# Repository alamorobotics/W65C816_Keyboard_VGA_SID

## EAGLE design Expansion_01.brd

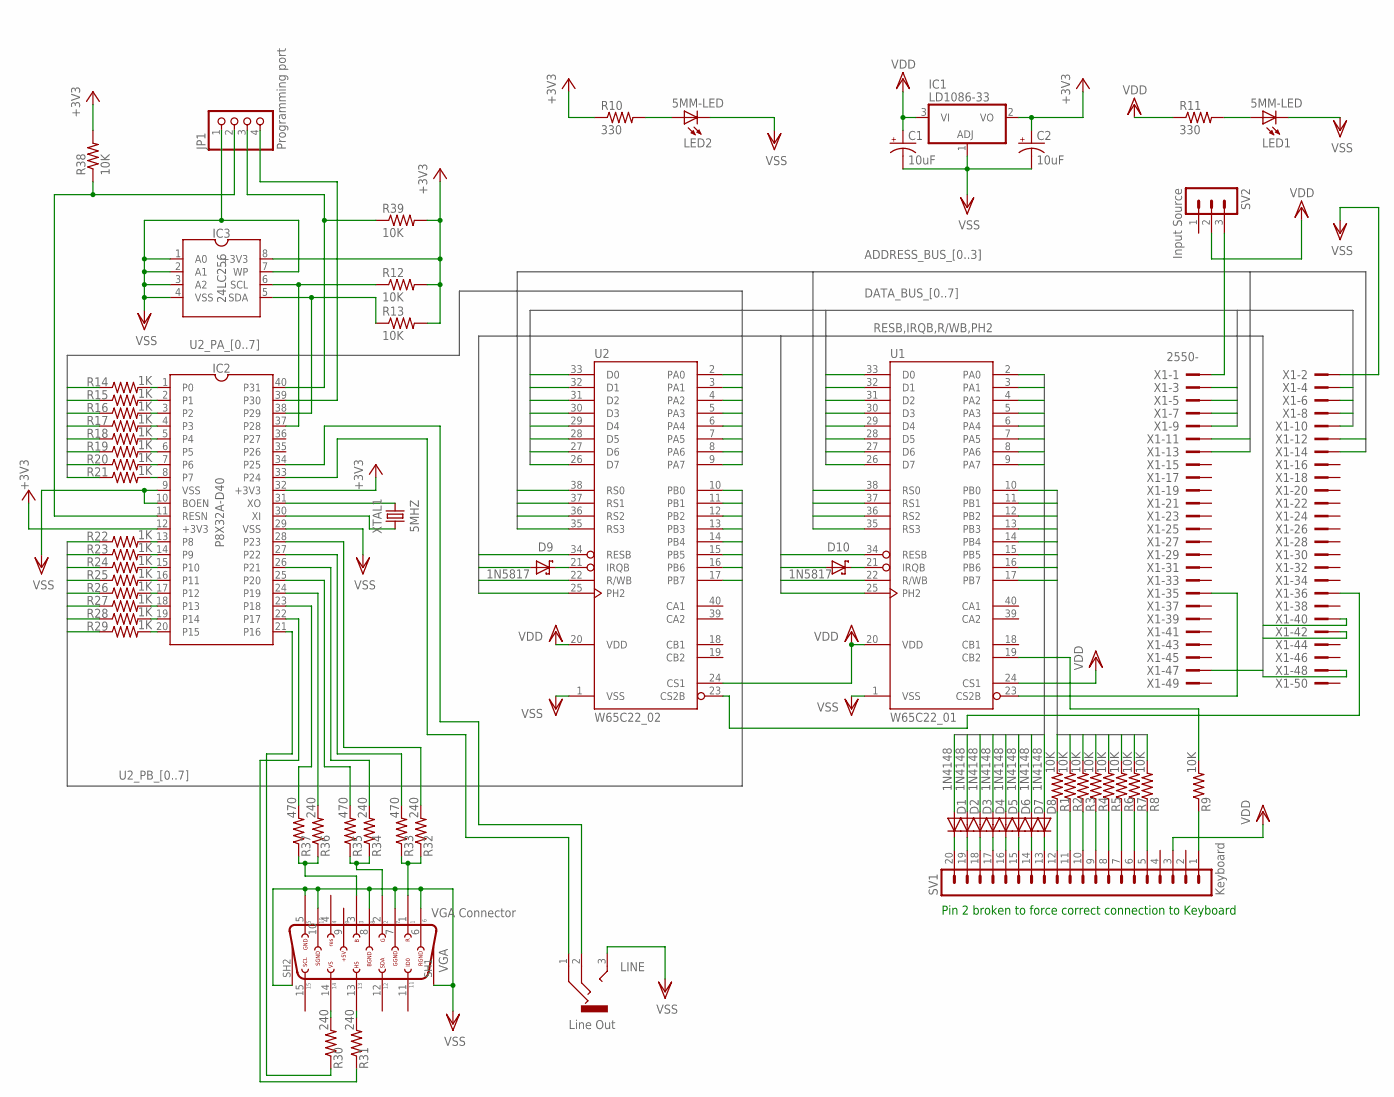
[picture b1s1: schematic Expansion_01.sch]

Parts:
C1, C2: 10uF; E2-5
D1, D2, D3, D4, D5, D6, D7, D8: 1N4148; DO35-7
D9, D10: 1N5817; DO41-7.6
IC1: LD1086-33; TO220H
IC2: P8X32A-D40DIP-40; P8X32A-D40
IC3: 24LC256DIP-8; 24LC256
JP1: Programming port; 1X04/90
LED1, LED2: 5MM-LED
LINE: Line Out; 1503_04
R1, R2, R3, R4, R5, R6, R7, R8, R9, R12, R13, R38, R39: 10K; 0207/10
R10, R11: 330; 0207/10
R14, R15, R16, R17, R18, R19, R20, R21, R22, R23, R24, R25, R26, R27, R28, R29: 1K; 0207/10
R30, R31, R32, R34, R36: 240; 0207/10
R33, R35, R37: 470; 0207/10
SV1: Keyboard; MA20-1
SV2: Input Source; MA03-1
U1: W65C22_01; DIP-40
U2: W65C22_02; DIP-40
VGA: VGA Connector; HD15F
X1: 2550-; PAK100/2500-50
XTAL1: 5MHZ; 5MHZ-CRYSTAL

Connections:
+3V3: C2.+, IC1.2 (VO), IC2.12 (+3V3), IC2.32 (+3V3), IC3.8 (+3V3), R10.1, R12.2, R13.2, R38.2, R39.2
ADDRESS_BUS_0: U1.38 (RS0), U2.38 (RS0), X1.11
ADDRESS_BUS_1: U1.37 (RS1), U2.37 (RS1), X1.12
ADDRESS_BUS_2: U1.36 (RS2), U2.36 (RS2), X1.13
ADDRESS_BUS_3: U1.35 (RS3), U2.35 (RS3), X1.14
DATA_BUS_0: U1.33 (D0), U2.33 (D0), X1.3, X1.4
DATA_BUS_1: U1.32 (D1), U2.32 (D1)
DATA_BUS_2: U1.31 (D2), U2.31 (D2), X1.5
DATA_BUS_3: U1.30 (D3), U2.30 (D3), X1.6
DATA_BUS_4: U1.29 (D4), U2.29 (D4), X1.7
DATA_BUS_5: U1.28 (D5), U2.28 (D5), X1.8
DATA_BUS_6: U1.27 (D6), U2.27 (D6), X1.9
DATA_BUS_7: U1.26 (D7), U2.26 (D7), X1.10
IRQB: D9.A, D10.A, X1.40
unnamed: SV2.3, X1.1
unnamed: D1.C, SV1.20
unnamed: D2.C, SV1.19
unnamed: D3.C, SV1.18
unnamed: D4.C, SV1.17
unnamed: D5.C, SV1.16
unnamed: D6.C, SV1.15
unnamed: D7.C, SV1.14
unnamed: D8.C, SV1.13
unnamed: R1.1, SV1.12
unnamed: R2.1, SV1.11
unnamed: R3.1, SV1.10
unnamed: R4.1, SV1.9
unnamed: R5.1, SV1.8
unnamed: R6.1, SV1.7
unnamed: R7.1, SV1.6
unnamed: R8.1, SV1.5
unnamed: R9.1, SV1.1
unnamed: R9.2, U1.19 (CB2)
unnamed: D10.C, U1.21 (IRQB)
unnamed: D9.C, U2.21 (IRQB)
unnamed: U1.23 (CS2B), X1.35
unnamed: U2.23 (CS2B), X1.36
unnamed: LED1.A, R11.2
unnamed: LED2.A, R10.2
unnamed: IC2.40 (P31), JP1.3, R39.1
unnamed: IC2.39 (P30), JP1.4
unnamed: IC2.31 (XO), XTAL1.2
unnamed: IC2.30 (XI), XTAL1.1
unnamed: IC2.11 (RESN), JP1.2, R38.1
unnamed: IC2.38 (P29), IC3.5 (SDA), R13.1
unnamed: IC2.37 (P28), IC3.6 (SCL), R12.1
unnamed: IC2.1 (P0), R14.2
unnamed: IC2.2 (P1), R15.2
unnamed: IC2.3 (P2), R16.2
unnamed: IC2.4 (P3), R17.2
unnamed: IC2.5 (P4), R18.2
unnamed: IC2.6 (P5), R19.2
unnamed: IC2.7 (P6), R20.2
unnamed: IC2.8 (P7), R21.2
unnamed: IC2.13 (P8), R22.2
unnamed: IC2.14 (P9), R23.2
unnamed: IC2.15 (P10), R24.2
unnamed: IC2.16 (P11), R25.2
unnamed: IC2.17 (P12), R26.2
unnamed: IC2.18 (P13), R27.2
unnamed: IC2.19 (P14), R28.2
unnamed: IC2.20 (P15), R29.2
unnamed: R32.1, R33.1, VGA.1
unnamed: R34.1, R35.1, VGA.2
unnamed: R36.1, R37.1, VGA.3
unnamed: IC2.23 (P18), R37.2
unnamed: IC2.22 (P17), R31.1
unnamed: R30.2, VGA.14
unnamed: R31.2, VGA.13
unnamed: IC2.21 (P16), R30.1
unnamed: IC2.24 (P19), R36.2
unnamed: IC2.25 (P20), R35.2
unnamed: IC2.26 (P21), R34.2
unnamed: IC2.27 (P22), R33.2
unnamed: IC2.28 (P23), R32.2
unnamed: IC2.33 (P24), LINE.1
unnamed: IC2.34 (P25), LINE.2 (3)
PH2: U1.25 (PH2), U2.25 (PH2), X1.48
R/WB: U1.22 (R/WB), U2.22 (R/WB), X1.47
RESB: U1.34 (RESB), U2.34 (RESB), X1.42
U1_PA_0: D1.A, U1.2 (PA0)
U1_PA_1: D2.A, U1.3 (PA1)
U1_PA_2: D3.A, U1.4 (PA2)
U1_PA_3: D4.A, U1.5 (PA3)
U1_PA_4: D5.A, U1.6 (PA4)
U1_PA_5: D6.A, U1.7 (PA5)
U1_PA_6: D7.A, U1.8 (PA6)
U1_PA_7: D8.A, U1.9 (PA7)
U1_PB_0: R1.2, U1.10 (PB0)
U1_PB_1: R2.2, U1.11 (PB1)
U1_PB_2: R3.2, U1.12 (PB2)
U1_PB_3: R4.2, U1.13 (PB3)
U1_PB_4: R5.2, U1.14 (PB4)
U1_PB_5: R6.2, U1.15 (PB5)
U1_PB_6: R7.2, U1.16 (PB6)
U1_PB_7: R8.2, U1.17 (PB7)
U2_PA_0: R14.1, U2.2 (PA0)
U2_PA_1: R15.1, U2.3 (PA1)
U2_PA_2: R16.1, U2.4 (PA2)
U2_PA_3: R17.1, U2.5 (PA3)
U2_PA_4: R18.1, U2.6 (PA4)
U2_PA_5: R19.1, U2.7 (PA5)
U2_PA_6: R20.1, U2.8 (PA6)
U2_PA_7: R21.1, U2.9 (PA7)
U2_PB_0: R22.1, U2.10 (PB0)
U2_PB_1: R23.1, U2.11 (PB1)
U2_PB_2: R24.1, U2.12 (PB2)
U2_PB_3: R25.1, U2.13 (PB3)
U2_PB_4: R26.1, U2.14 (PB4)
U2_PB_5: R27.1, U2.15 (PB5)
U2_PB_6: R28.1, U2.16 (PB6)
U2_PB_7: R29.1, U2.17 (PB7)
VDD: C1.+, IC1.3 (VI), R11.1, SV1.3, SV2.2, U1.20 (VDD), U1.24 (CS1), U2.20 (VDD), U2.24 (CS1)
VSS: C1.-, C2.-, IC1.1 (ADJ), IC2.9 (VSS), IC2.10 (BOEN), IC2.29 (VSS), IC3.1 (A0), IC3.2 (A1), IC3.3 (A2), IC3.4 (VSS), IC3.7 (WP), JP1.1, LED1.K (C), LED2.K (C), LINE.3 (2), U1.1 (VSS), U2.1 (VSS), VGA.5, VGA.6, VGA.7, VGA.8, VGA.10, VGA.SH1, VGA.SH2, X1.2

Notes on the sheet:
Pin 2 broken to force correct connection to Keyboard

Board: 2 copper layers, 65 parts (0 on the bottom side), 114 nets, no tracks yet.

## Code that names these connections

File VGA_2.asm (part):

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
; Transfer from W65C816SXB to Propeller

; 1. W65C816SXB waits for PB7 (P15) to be low, $80
; 2. W65C816SXB puts data on PIA PA
; 3. W65C816SXB puts data on PIA PB with PB6 high. $40
; 4. Propeller waits for PB6 (P14) to go high.
; 5. Propeller reads PIA PA-PB and sets P15 high.
; 6, W65C816SXB waits for PB7 (P15)to be high, $80
; 7. W65C816SXB sets PIA PB6 (P14) low. $40
; 8. Propeller waits for PB6 (P14) to go low.
; 9. Propeller does it's thing...
; 10. Propeller sets P15 Low.

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
;########################### PIN ASSIGNMENTS #####################

;  P0  - Data 0 - PIA PA0 via 1Kohm resistor
;  P1  - Data 1 - PIA PA1 via 1Kohm resistor
;  P2  - Data 2 - PIA PA2 via 1Kohm resistor
;  P3  - Data 3 - PIA PA3 via 1Kohm resistor 
;  P4  - Data 4 - PIA PA4 via 1Kohm resistor 
;  P5  - Data 5 - PIA PA5 via 1Kohm resistor
;  P6  - Data 6 - PIA PA6 via 1Kohm resistor
;  P7  - Data 7 - PIA PA7 via 1Kohm resistor
;  P8  - Address 0 - PIA PB0 via 1Kohm resistor
;  P9  - Address 1 - PIA PB1 via 1Kohm resistor
;  P10 - Address 2 - PIA PB2 via 1Kohm resistor
;  P11 - Address 3 - PIA PB3 via 1Kohm resistor
;  P12 - Address 4 - PIA PB4 via 1Kohm resistor
;  P13 - Address 5 - 0 for VGA and 1 for SID  - PIA PB5 via 1Kohm resistor
;  P14 - Flag Write - Wait for High from W65C816SXB, once propeller flag busy, W65C816SXB sets low. - PIA PB6 via 1Kohm resistor
;  P15 - Flag BUSY - Set high by propeller when processing. - PIA PB7 via 1Kohm resistor, only input...    
;  P16 - VGA VSync - 270 ohm resistor to D-Sub 14
;  P17 - VGA HSync - 270 ohm resistor to D-Sub 13 
;  P18 - VGA B0 - 560 ohm resistor to D-Sub 3
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
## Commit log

2016-01-23 :octocat: Added .gitattributes & .gitignore files
2016-01-25 Version 1.0
    Added first VIA...
2016-01-27 Added schematics.
    Added schematics.
2016-01-30 Finished schematics
    Finished schematics
2016-02-05 Propeller files etc...
    Propeller files etc...
2016-02-17 Fixed Schematics
    Fixed Schematics
2016-02-17 Cleanup
    Cleanup
